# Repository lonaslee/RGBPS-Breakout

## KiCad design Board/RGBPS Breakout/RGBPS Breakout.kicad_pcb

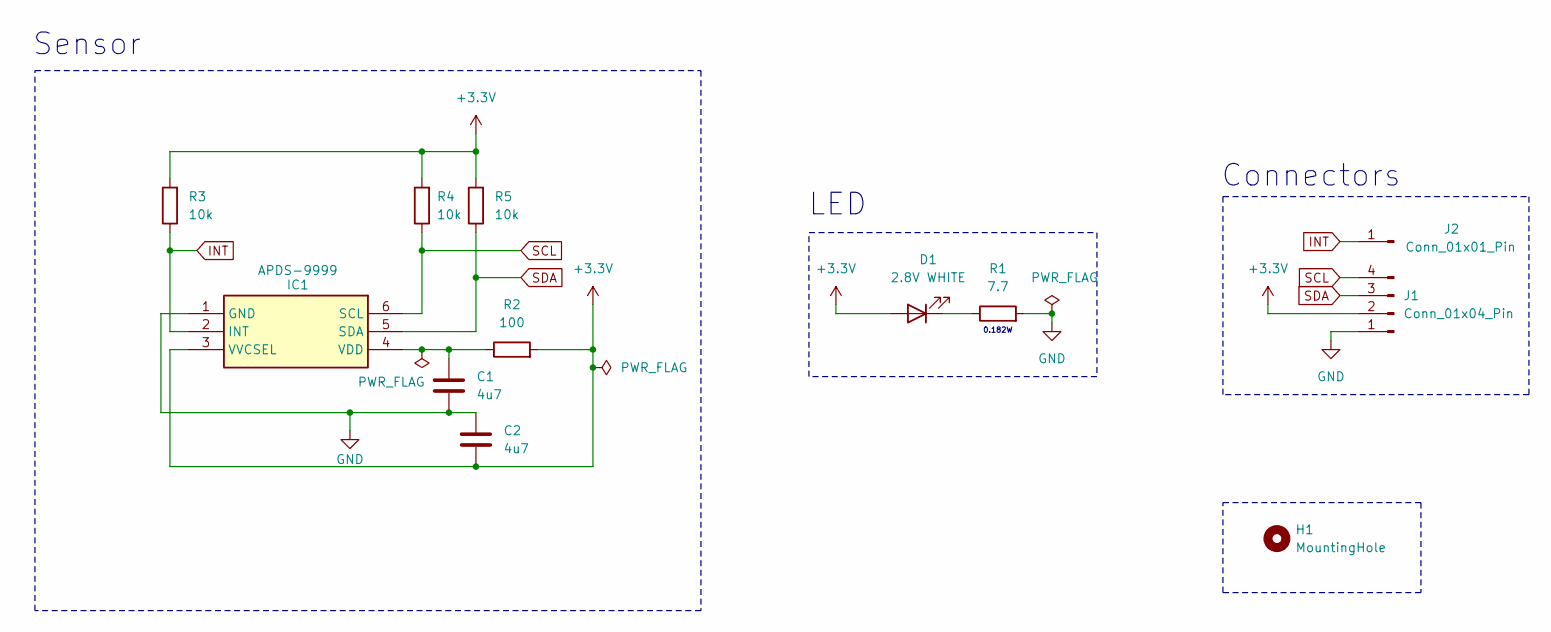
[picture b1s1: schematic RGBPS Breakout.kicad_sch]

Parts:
C1, C2: 4u7; C_0402_1005Metric
D1: 2.8V WHITE; LED_1206_3216Metric
H1: MountingHole; MountingHole_2.5mm
IC1: APDS-9999; APDS9999; Mouser Part Number 630-APDS-9999
J1: Conn_01x04_Pin; JST_PH_S4B-PH-K_1x04_P2.00mm_Horizontal
J2: Conn_01x01_Pin; PinHeader_1x01_P2.54mm_Vertical
R1: 7.7; R_0402_1005Metric
R2: 100; R_0402_1005Metric
R3, R4, R5: 10k; R_0402_1005Metric

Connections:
+3.3V: C2.2, D1.2 (A), IC1.3 (VVCSEL), J1.2, R2.2, R3.2, R4.2, R5.2
GND: C1.2, C2.1, IC1.1 (GND), J1.1, R1.2
INT: IC1.2 (INT), J2.1, R3.1
unnamed: D1.1 (K), R1.1
unnamed: C1.1, IC1.4 (VDD), R2.1
SCL: IC1.6 (SCL), J1.4, R4.1
SDA: IC1.5 (SDA), J1.3, R5.1

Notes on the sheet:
Sensor
0.182W
Connectors
LED

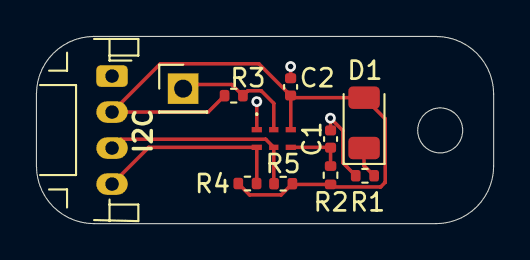
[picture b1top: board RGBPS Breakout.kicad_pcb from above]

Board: 2 copper layers, 25.4 x 10.4 mm, 12 parts (0 on the bottom side), 7 nets.

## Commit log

2024-07-05 configure apds footprint from mouser
2024-07-05 kicad setup
2024-07-05 connector
2024-07-05 indicator/illuminating LED
2024-07-05 partially done with power
2024-07-05 i2c wiring + pullup resistors
2024-07-05 interrupt pin
2024-07-05 footprints except for the sensor
2024-07-05 label
2024-07-05 pass electrical rules check finally
2024-07-05 place pcb
2024-07-05 bruuh footprint file is broken
2024-07-05 start routing, add zone fill for ground
2024-07-09 routing
2024-07-09 manufacturing files
